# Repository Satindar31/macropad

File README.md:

# Macropad!!!
### BOM
- PCB
- LED x2
- Xiao rp2040
- Keys x4

## Images
### Schematic

### PCB

### Case + PCB

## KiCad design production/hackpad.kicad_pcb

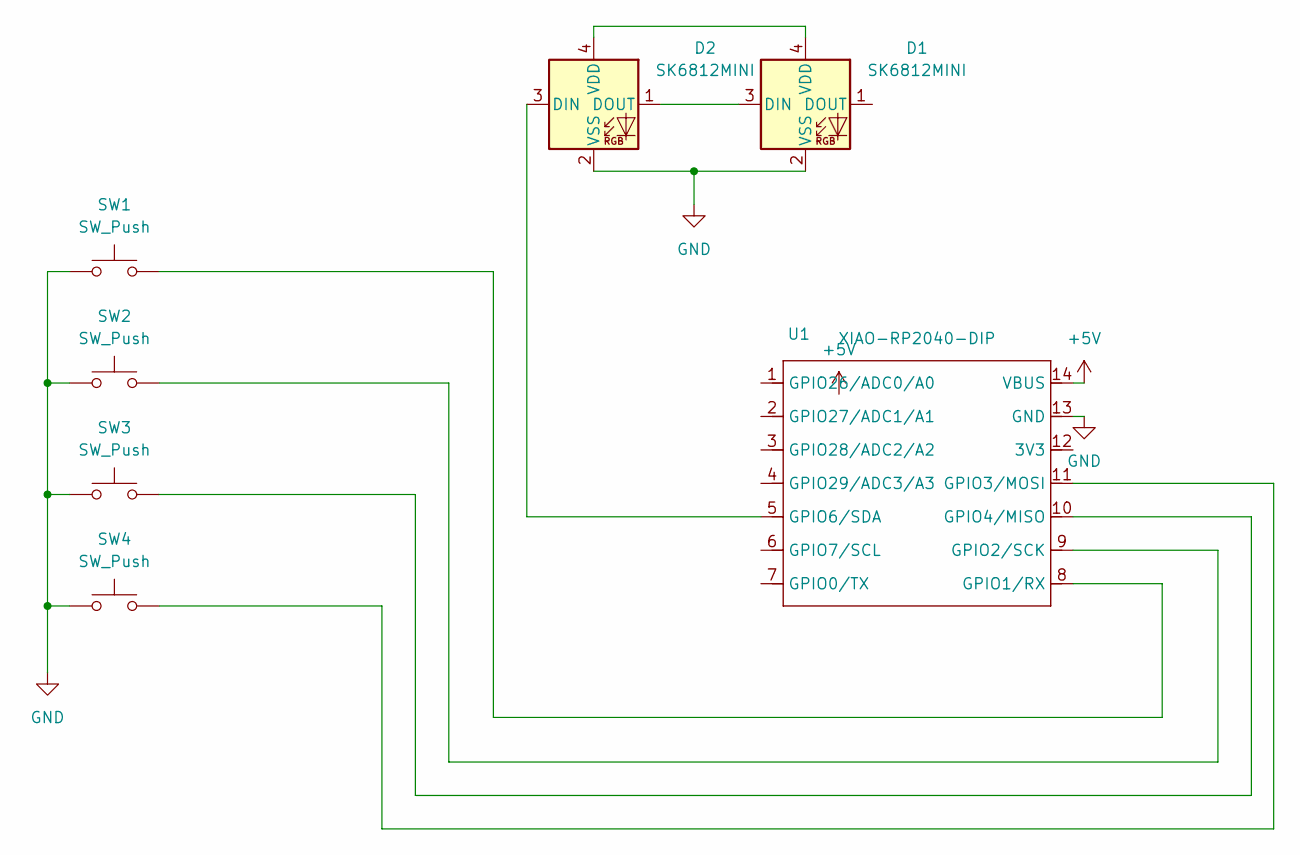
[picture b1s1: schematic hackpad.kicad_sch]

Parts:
D1, D2: SK6812MINI; LED_SK6812MINI_PLCC4_3.5x3.5mm_P1.75mm
SW1, SW2, SW3, SW4: SW_Push; SW_Cherry_MX_1.00u_PCB
U1: XIAO-RP2040-DIP

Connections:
+5V: U1.14 (VBUS)
GND: D1.2 (VSS), D2.2 (VSS), SW1.1, SW2.1, SW3.1, SW4.1, U1.13 (GND)
unnamed: D1.3 (DIN), D2.1 (DOUT)
unnamed: D1.4 (VDD), D2.4 (VDD)
unnamed: D2.3 (DIN), U1.5 (GPIO6/SDA)
unnamed: SW1.2, U1.8 (GPIO1/RX)
unnamed: SW2.2, U1.9 (GPIO2/SCK)
unnamed: SW4.2, U1.11 (GPIO3/MOSI)
unnamed: SW3.2, U1.10 (GPIO4/MISO)

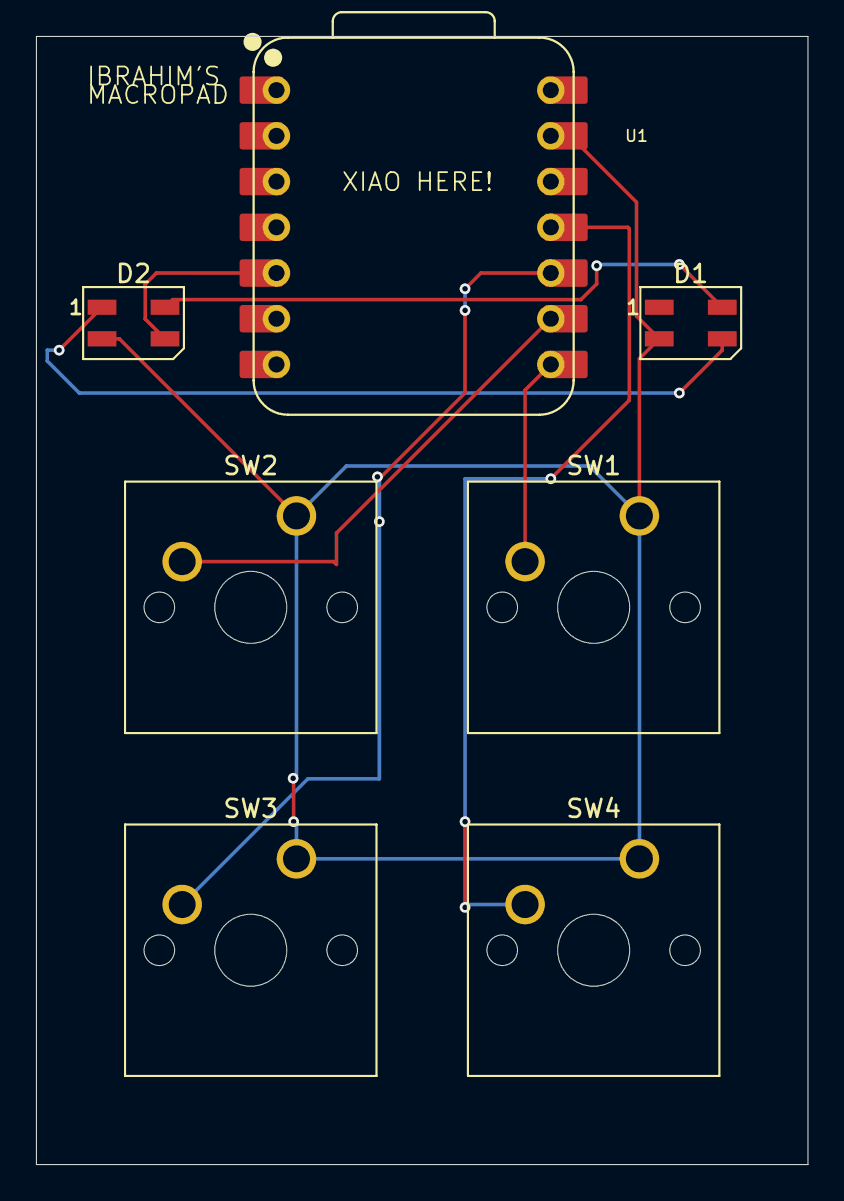
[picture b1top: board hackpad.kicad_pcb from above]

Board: 2 copper layers, 42.9 x 62.7 mm, 7 parts (0 on the bottom side), 8 nets.
